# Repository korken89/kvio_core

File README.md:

# KVision Core - Visual Inertial Core

KVision core is an FPGA based Visual Inertial Odometry accelerator.

More info to come.

---

## Contributors

List of contributors in alphabetical order:

* Emil Fresk ([@korken89](https://github.com/korken89))

---

## License

The hardware is OSHW using the Cern-OHL license.

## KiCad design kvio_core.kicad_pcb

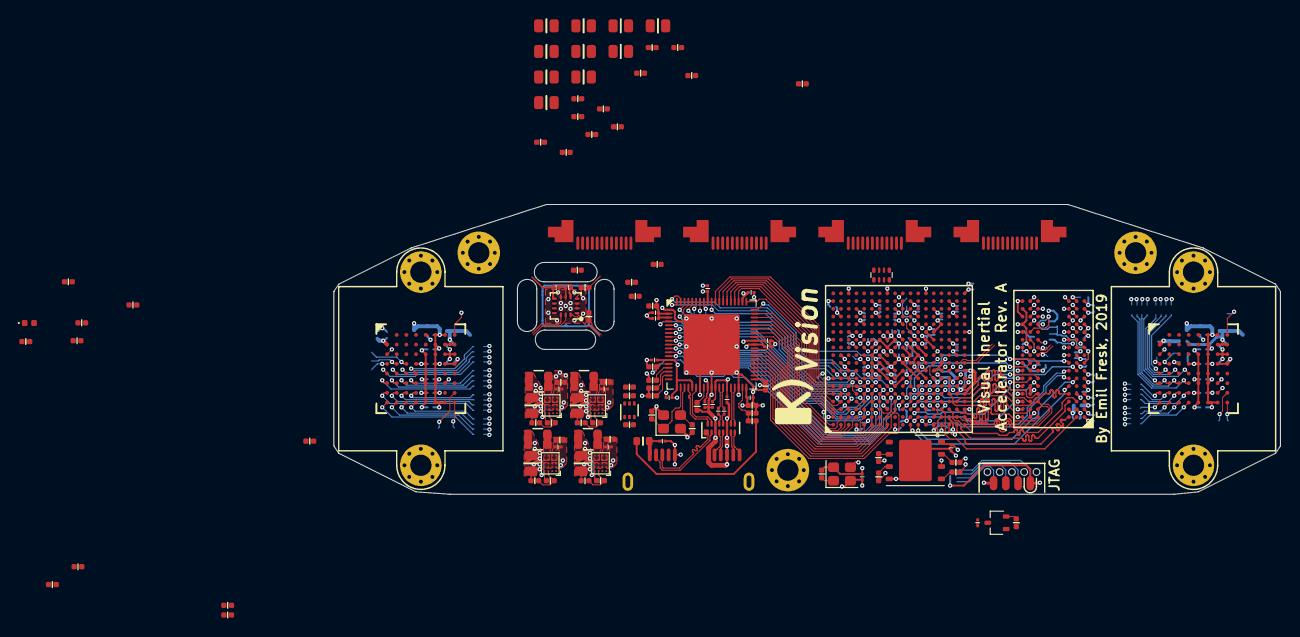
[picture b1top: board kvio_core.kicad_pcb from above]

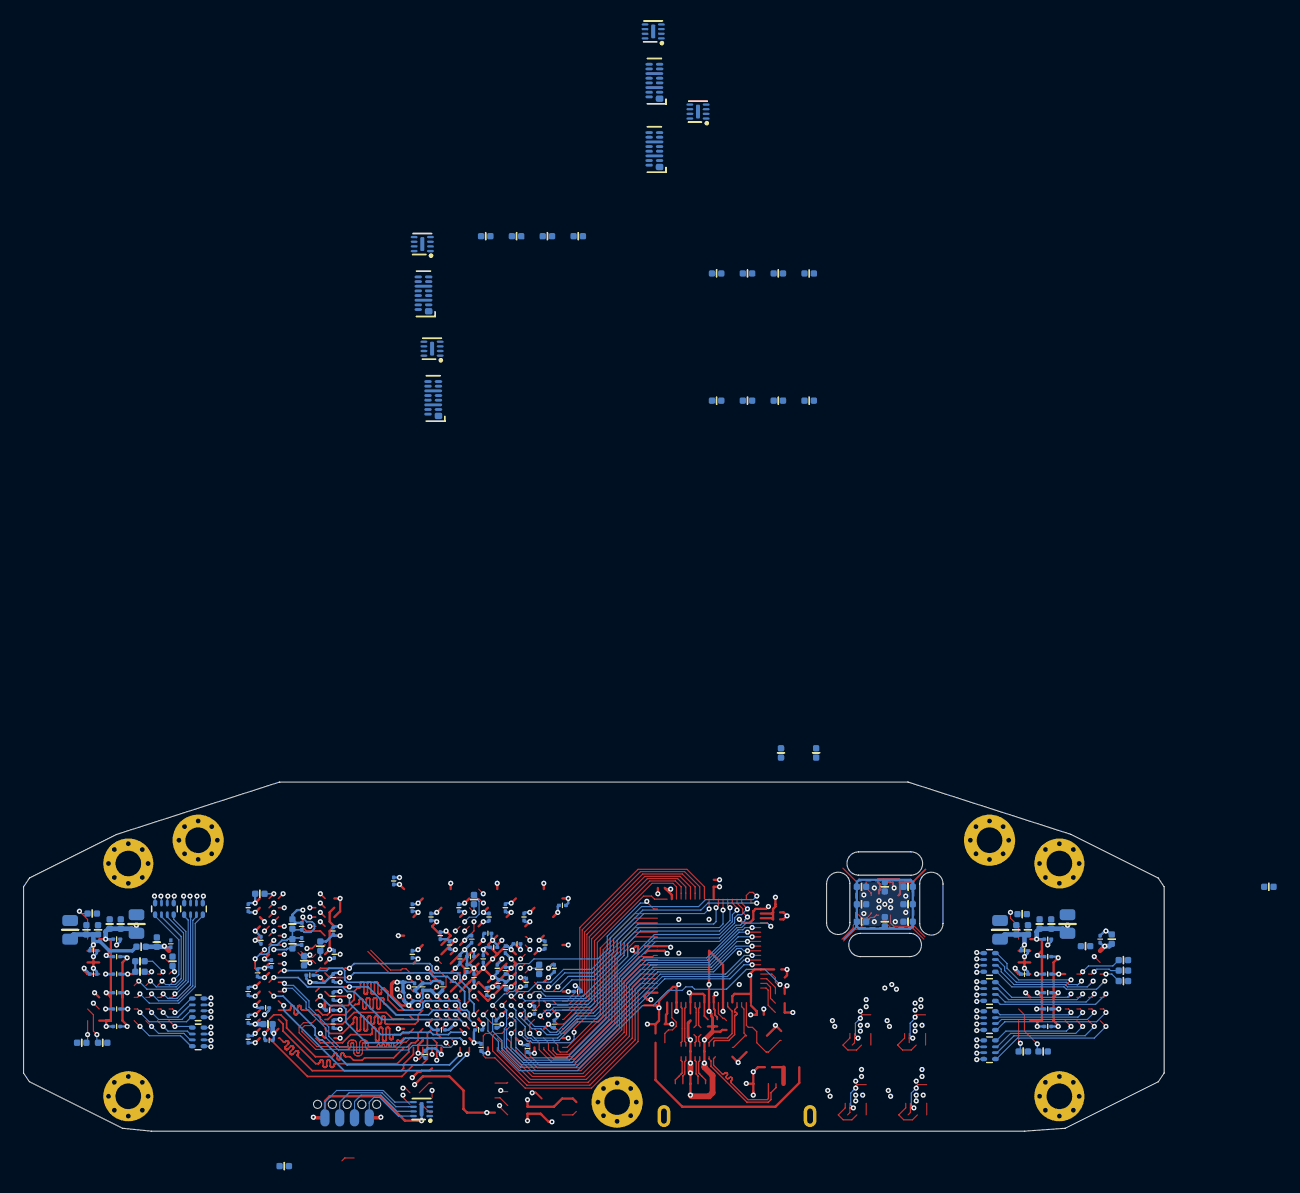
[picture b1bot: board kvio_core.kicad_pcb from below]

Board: 6 copper layers, 98.0 x 30.0 mm, 287 parts (154 on the bottom side), 316 nets.

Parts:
C101, C215, C216, C220, C221, C223, C224, C226, C227, C229, C230, C231, C232, C233, C234, C235, C236, C237, C240, C241, C243, C244, C245, C248, C249, C251, C252, C253, C254, C255, C261, C262, C263, C264, C265, C266, C267, C268, C269, C270, C272, C275, C278, C281, C284, C285, C301, C302, C1105, C1106, C1110, C1111, C1112, C1113, C1114, C1115, C1116, C1201, C1202, C1204, C1206, C1207, C1208, C1209, C1210, C1211, C1212, C1213, C1214, C1215, C1216, C1217, C1218, C1219, C1220, C1221, C1222, C1301, C1302, C1303, C1306, C1308, C1309, C1310, C1313, C1314, C1315, C1316, C1317, C1318, C1320, C1321, C1405, C1406, C1410, C1411, C1412, C1413, C1414, C1415, C1416: 0.1u; C_0201
C201, C202, C203, C204, C207, C208, C209, C214, C238, C239, C273, C276, C279, C282, C1101, C1104, C1401, C1404: 47u; C_0805
C205, C206, C210, C211, C212, C213, C217, C218, C219, C225, C228, C246, C247, C401, C801, C901, C1001, C1102, C1103, C1107, C1108, C1109, C1203, C1205, C1305, C1307, C1319, C1402, C1403, C1407, C1408, C1409: 4.7u; C_0402
C271, C274, C277, C280: 10u; C_0402
C1311, C1312: 18p; C_0402
D301: GREEN; LED_0402_1005Metric
FB201, FB401, FB801, FB901, FB1001, FB1101, FB1201, FB1401: Ferrite_Bead_Small; R_0402
FB1301: BLM18KG102SH1D; R_0603
H101, H102, H103: MountingHole_Pad; MountingHole_2.2mm_M2_Pad_Via
J401, J801, J901, J1001: 12-pin_FFC_(SFV12R); SFV12R
J1301: USB3_B_Micro; AMPHENOL-GSB343K33HR
L201, L202, L203, L204: 0.47uH; L_2025Metric
LH1101, LH1401: lens_holder; m12_20mm
Q1201: NTZD3155C; SOT-563
R101, R1101, R1102, R1103, R1104, R1302, R1303, R1306, R1401, R1402, R1403, R1404: 10k; R_0402
R201, R202, R203, R204, R205, R206, R207, R208: 0; R_0402
R301, R304, R311, R312, R313, R314, R401, R403, R801, R802, R901, R902, R1001, R1002, R1204, R1206, R1213, R1214, R1215, R1216, R1217: 100; R_0402
R302, R303, R1304, R1305: 470; R_0402
R307, R315, R316, R1205, R1207, R1208, R1210, R1307: 4.7k; R_0402
R308, R310, R1201, R1202: 1k; R_0402
R701, R702, R1105, R1106, R1301: 1.6k; R_0402
R1203: 240; R_0402
R1209, R1211, R1212, R1218, R1219, R1220, R1221, R1222: 180; R_0402
RN101, RN1101, RN1102, RN1103, RN1104, RN1401, RN1402, RN1403, RN1404: 22; R_Array_Convex_4x0402
U101: xc7a100t-csg324; CSG324_Artix7_100T
U102: 100 MHz; Crystal_SMD_2520-4Pin_2.5x2.0mm
U201, U202, U203, U204: FAN53541; WLCSP-20_1.96x1.56mm_Layout4x5_P0.4mm
U301: MX25L6433F; WSON-8-1EP_6x5mm_P1.27mm_EP3.4x4.3mm
U302: MAX809; SOT-323
U303, U402, U801, U901, U1001: IP4254CZ8-4-TTL; UDFN-8-1EP_1.7x1.35mm_P0.4mm_EP0.4x1.2mm
U304: SOICbite_JTAG; SOICbiteSmall
U401, U802, U902, U1002, U1302: EMI8143; XDFN-16_1.35x3.5mm
U1101, U1401: AR0135CS
U1201: MT41J128M16JT-125:K; BGA-96_8.0x14.0mm_DDR16
U1202: ASM330LHH; LGA-14-2.5x3
U1301: FT601Q; QFN-76-1EP_9x9mm_P0.4mm_EP5.8x6.3mm
Y1301: Crystal_GND24_Small; Crystal_SMD_2520-4Pin_2.5x2.0mm

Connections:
+1V0: C209.1, C214.1, C219.1, C225.1, C231.1, C237.1, C239.1, C245.1, C253.1, C255.1, C261.1, C263.1, C266.1, C267.1, C268.1, C269.1, C270.1, C282.1, L204.2, R207.1, U101.F8, U101.F10, U101.G7, U101.G9, U101.G11, U101.H8, U101.J7, U101.J11, U101.K8, U101.L7, U101.L11, U101.M8, U101.M10, U101.N7, U101.N9, U101.N11, U204.A4
+1V5: C201.1, C205.1, C210.1, C215.1, C220.1, C226.1, C232.1, C240.1, C248.1, C279.1, L203.2, R205.1, U101.K4, U101.N3, U101.P6, U101.T2, U101.U5, U101.V8, U203.A4
+1V8: C203.1, C207.1, C212.1, C217.1, C223.1, C229.1, C235.1, C238.1, C243.1, C246.1, C247.1, C251.1, C254.1, C262.1, C264.1, C265.1, C276.1, C1101.1, C1102.1, C1103.1, C1105.1, C1106.1, C1110.1, C1111.1, C1115.1, C1116.1, C1401.1, C1402.1, C1403.1, C1405.1, C1406.1, C1410.1, C1411.1, C1415.1, C1416.1, FB201.2, L202.2, R203.1, R701.2, R702.2, R1105.2, R1106.2, U101.A17, U101.C13, U101.D16, U101.E8, U101.F12, U101.G15, U101.H12, U101.H18, U101.K12, U101.K14, U101.M12, U202.A4, U1101.A6, U1101.A7, U1101.B6, U1101.C6, U1101.D6, U1101.E6, U1101.F6, U1101.G6, U1101.H6, U1101.H7, U1401.A6, U1401.A7, U1401.B6, U1401.C6, U1401.D6, U1401.E6, U1401.F6, U1401.G6, U1401.H6, U1401.H7
+3V3: C101.1, C202.1, C204.1, C206.1, C208.1, C211.1, C213.1, C216.1, C218.1, C221.1, C224.1, C227.1, C228.1, C230.1, C233.1, C234.1, C236.1, C241.1, C244.1, C249.1, C252.1, C273.1, C284.1, C301.2, C302.2, C1305.1, C1306.1, C1308.1, C1309.1, C1313.1, C1314.1, C1316.1, C1317.1, FB1201.2, L201.2, R101.1, R201.1, R302.2, R307.1, R308.1, R315.1, R316.1, R1302.1, U101.A7, U101.B10, U101.C3, U101.D6, U101.F2, U101.G5, U101.J1, U101.L17, U101.N13, U101.P8, U101.P12, U101.P16, U101.R9, U101.T12, U101.U15, U101.V18, U102.4, U201.A4, U301.8, U302.3, U1301.14, U1301.20, U1301.24, U1301.28, U1301.38, U1301.49, U1301.59, U1301.68
/CAM0_CLK: RN101.8, U1401.C1
/CAM0_CLK_P: RN101.1, U101.F18
/CAM0_D0: RN1402.8, U101.B14
/CAM0_D1: RN1402.7, U101.B12
/CAM0_D2: RN1402.6, U101.B11
/CAM0_D3: RN1402.5, U101.A11
/CAM0_D4: RN1403.8, U101.F13
/CAM0_D5: RN1403.7, U101.F14
/CAM0_D6: RN1403.6, U101.D12
/CAM0_D7: RN1403.5, U101.D13
/CAM0_D8: RN1404.8, U101.B16
/CAM0_D9: RN1404.7, U101.B17
/CAM0_D10: RN1404.6, U101.A15
/CAM0_D11: RN1404.5, U101.A16
/CAM0_FLASH: RN1401.1, U101.A18
/CAM0_FV: RN1401.3, U101.A13
/CAM0_LV: RN1401.4, U101.A14
/CAM0_PIXCLK: RN1401.2, U101.D15
/CAM0_RESET: R1404.1, U101.C12, U1401.H8
/CAM0_SCLK: R702.1, U101.E16, U1401.D2
/CAM0_SDATA: R701.1, U101.E15, U1401.D3
/CAM0_TRIGGER: RN101.7, U1401.G7
/CAM0_TRIGGER_P: RN101.2, U101.B18
/CAM1_CLK: RN101.6, U1101.C1
/CAM1_CLK_P: RN101.3, U101.G18
/CAM1_D0: RN1102.8, U101.H16
/CAM1_D1: RN1102.7, U101.G16
/CAM1_D2: RN1102.6, U101.F15
/CAM1_D3: RN1102.5, U101.F16
/CAM1_D4: RN1103.8, U101.H14
/CAM1_D5: RN1103.7, U101.G14
/CAM1_D6: RN1103.6, U101.E17
/CAM1_D7: RN1103.5, U101.D17
/CAM1_D8: RN1104.8, U101.K13
/CAM1_D9: RN1104.7, U101.J13
/CAM1_D10: RN1104.6, U101.H17
/CAM1_D11: RN1104.5, U101.G17
/CAM1_FLASH: RN1101.1, U101.C17
/CAM1_FV: RN1101.3, U101.J14
/CAM1_LV: RN1101.4, U101.H15
/CAM1_PIXCLK: RN1101.2, U101.C15
/CAM1_RESET: R1101.1, U101.B13, U1101.H8
/CAM1_SCLK: R1106.1, U101.D18, U1101.D2
/CAM1_SDATA: R1105.1, U101.E18, U1101.D3
/CAM1_TRIGGER: RN101.5, U1101.G7
/CAM1_TRIGGER_P: RN101.4, U101.C16
/Camera 1/5V_CAM: C401.1, FB401.1, J401.12
/Camera 1/CLK_N: R403.2, U401.12
/Camera 1/CLK_P: R403.1, U401.13
/Camera 1/CLK_P_N: J401.5, U401.5
/Camera 1/CLK_P_P: J401.6, U401.4
/Camera 1/D1_N: R401.2, U401.9
/Camera 1/D1_P: R401.1, U401.10
/Camera 1/D1_P_N: J401.2, U401.8
/Camera 1/D1_P_P: J401.3, U401.7
/Camera 1/IO1_P: J401.8, U402.8
/Camera 1/IO2_P: J401.9, U402.7
/Camera 1/SCL_P: J401.11, U402.5
/Camera 1/SDA_P: J401.10, U402.6
/Camera 2/5V_CAM: C801.1, FB801.1, J801.12
/Camera 2/CLK_N: R802.2, U802.12
/Camera 2/CLK_P: R802.1, U802.13
/Camera 2/CLK_P_N: J801.5, U802.5
/Camera 2/CLK_P_P: J801.6, U802.4
/Camera 2/D1_N: R801.2, U802.9
/Camera 2/D1_P: R801.1, U802.10
/Camera 2/D1_P_N: J801.2, U802.8
/Camera 2/D1_P_P: J801.3, U802.7
/Camera 2/IO1_P: J801.8, U801.8
/Camera 2/IO2_P: J801.9, U801.7
/Camera 2/SCL_P: J801.11, U801.5
/Camera 2/SDA_P: J801.10, U801.6
/Camera 3/5V_CAM: C901.1, FB901.1, J901.12
/Camera 3/CLK_N: R902.2, U902.12
/Camera 3/CLK_P: R902.1, U902.13
/Camera 3/CLK_P_N: J901.5, U902.5
/Camera 3/CLK_P_P: J901.6, U902.4
/Camera 3/D1_N: R901.2, U902.9
/Camera 3/D1_P: R901.1, U902.10
/Camera 3/D1_P_N: J901.2, U902.8
/Camera 3/D1_P_P: J901.3, U902.7
/Camera 3/IO1_P: J901.8, U901.8
/Camera 3/IO2_P: J901.9, U901.7
/Camera 3/SCL_P: J901.11, U901.5
/Camera 3/SDA_P: J901.10, U901.6
/Camera 4/5V_CAM: C1001.1, FB1001.1, J1001.12
/Camera 4/CLK_N: R1002.2, U1002.12
/Camera 4/CLK_P: R1002.1, U1002.13
/Camera 4/CLK_P_N: J1001.5, U1002.5
/Camera 4/CLK_P_P: J1001.6, U1002.4
/Camera 4/D1_N: R1001.2, U1002.9
/Camera 4/D1_P: R1001.1, U1002.10
/Camera 4/D1_P_N: J1001.2, U1002.8
/Camera 4/D1_P_P: J1001.3, U1002.7
/Camera 4/IO1_P: J1001.8, U1001.8
/Camera 4/IO2_P: J1001.9, U1001.7
/Camera 4/SCL_P: J1001.11, U1001.5
/Camera 4/SDA_P: J1001.10, U1001.6
/Config/CFG_CLK: R301.1, R304.1, U301.6
/Config/CFG_CS: R307.2, U101.L13, U301.1
/Config/CFG_D0: R311.1, U101.K17
/Config/CFG_D1: R312.1, U101.K18
/Config/CFG_D2: R313.1, R316.2, U101.L14
/Config/CFG_D3: R314.1, R315.2, U101.M14
/Config/CFG_DONE: R302.1, R303.2, U101.P10
/Config/CFG_INIT_B: R310.1, U101.P7, U101.P9
/Config/CFG_PUDC: R308.2, U101.L15
/Config/SYSTEM_RESET: R310.2, U302.2
/Config/TCK: U101.E10, U303.3
/Config/TCK_P: U303.6, U304.7
/Config/TDI: U101.E11, U303.4
/Config/TDI_P: U303.5, U304.8
/Config/TDO: U101.E13, U303.2
/Config/TDO_P: U303.7, U304.6
/Config/TMS: U101.E12, U303.1
/Config/TMS_P: U303.8, U304.5
/DDR Memory/A0: U101.U6, U1201.N3
/DDR Memory/A1: U101.R6, U1201.P7
/DDR Memory/A2: U101.V7, U1201.P3
/DDR Memory/A3: U101.V6, U1201.N2
/DDR Memory/A4: U101.T8, U1201.P8
/DDR Memory/A5: U101.P5, U1201.P2
/DDR Memory/A6: U101.R8, U1201.R8
/DDR Memory/A7: U101.N5, U1201.R2
/DDR Memory/A8: U101.R7, U1201.T8
/DDR Memory/A9: U101.N6, U1201.R3
/DDR Memory/A10: U101.P4, U1201.L7
/DDR Memory/A11: U101.N4, U1201.R7
/DDR Memory/A12: U101.U7, U1201.N7
/DDR Memory/A13: U101.M6, U1201.T3
/DDR Memory/BA0: U101.R5, U1201.M2
/DDR Memory/BA1: U101.U8, U1201.N8
/DDR Memory/BA2: U101.P3, U1201.M3
/DDR Memory/CAS_N: U101.R2, U1201.K3
/DDR Memory/CK_E: U101.T6, U1201.K9
/DDR Memory/CK_N: R1204.2, U101.V9, U1201.K7
/DDR Memory/CK_P: R1204.1, U101.U9, U1201.J7
/DDR Memory/CS_N: U101.P2, U1201.L2
/DDR Memory/DDR3_VDD: C1201.1, C1203.1, C1204.1, C1206.1, C1207.2, C1208.1, C1210.1, C1211.2, C1212.1, C1213.2, C1214.1, C1215.2, C1216.1, C1217.2, C1218.1, C1219.2, C1220.1, C1221.2, R1201.1, U1201.A1, U1201.A8, U1201.B2, U1201.C1, U1201.C9, U1201.D2, U1201.D9, U1201.E9, U1201.F1, U1201.G7, U1201.H2, U1201.H9, U1201.K2, U1201.K8, U1201.N1, U1201.N9, U1201.R1, U1201.R9
/DDR Memory/DQ0: U101.L1, U1201.E3
/DDR Memory/DQ1: U101.L4, U1201.F7
/DDR Memory/DQ2: U101.M1, U1201.F2
/DDR Memory/DQ3: U101.M3, U1201.F8
/DDR Memory/DQ4: U101.K3, U1201.H3
/DDR Memory/DQ5: U101.L6, U1201.H8
/DDR Memory/DQ6: U101.L3, U1201.G2
/DDR Memory/DQ7: U101.K5, U1201.H7
/DDR Memory/DQ8: U101.V5, U1201.D7
/DDR Memory/DQ9: U101.T3, U1201.C3
/DDR Memory/DQ10: U101.U4, U1201.C8
/DDR Memory/DQ11: U101.V1, U1201.C2
/DDR Memory/DQ12: U101.U3, U1201.A7
/DDR Memory/DQ13: U101.R3, U1201.A2
/DDR Memory/DQ14: U101.T5, U1201.B8
/DDR Memory/DQ15: U101.U1, U1201.A3
/DDR Memory/LDM: U101.M2, U1201.E7
/DDR Memory/LDQS_N: U101.N1, U1201.G3
/DDR Memory/LDQS_P: U101.N2, U1201.F3
/DDR Memory/ODT: U101.R1, U1201.K1
/DDR Memory/RAS_N: U101.T1, U1201.J3
/DDR Memory/RESET_N: R1205.1, U101.K6, U1201.T2
/DDR Memory/UDM: U101.V4, U1201.D3
/DDR Memory/UDQS_N: U101.V2, U1201.B7
/DDR Memory/UDQS_P: U101.U2, U1201.C7
/DDR Memory/VREF: C1201.2, C1202.1, R1201.2, R1202.1, U1201.H1, U1201.M8
/DDR Memory/WE_N: U101.M4, U1201.L3
/DDR Memory/ZQ: R1203.1, U1201.L8
/IMU_CS: R1215.1, U101.B9
/IMU_HEATER: R1206.2, U101.C11
/IMU_INT: R1210.1, R1217.1, U101.A8
/IMU_SCK: R1214.1, U101.C9
/IMU_SDI: R1213.1, U101.D9
/IMU_SDO: R1216.1, U101.B8
/Parallel camera/D0_P: RN1402.1, U1401.H1
/Parallel camera/D1_P: RN1402.2, U1401.H2
/Parallel camera/D2_P: RN1402.3, U1401.H3
/Parallel camera/D3_P: RN1402.4, U1401.H4
/Parallel camera/D4_P: RN1403.1, U1401.G1
/Parallel camera/D5_P: RN1403.2, U1401.G2
/Parallel camera/D6_P: RN1403.3, U1401.G3
/Parallel camera/D7_P: RN1403.4, U1401.G4
/Parallel camera/D8_P: RN1404.1, U1401.F1
/Parallel camera/D9_P: RN1404.2, U1401.F2
/Parallel camera/D10_P: RN1404.3, U1401.F3
/Parallel camera/D11_P: RN1404.4, U1401.F4
/Parallel camera/FLASH_P: RN1401.8, U1401.E4
/Parallel camera/FV_P: RN1401.6, U1401.E2
/Parallel camera/LV_P: RN1401.5, U1401.E1
/Parallel camera/PIXCLK_P: RN1401.7, U1401.E3
/Parallel camera/SADDR: R1402.1, U1401.D1
/Parallel camera/STANDBY: R1401.1, U1401.A8
/Parallel camera/VPLL: C1407.1, C1412.1, FB1401.1, U1401.B1
/Parallel camera/~OE: R1403.1, U1401.G8
/Power/SW10: L204.1, U204.D3, U204.D4, U204.E3, U204.E4
/Power/SW13: L203.1, U203.D3, U203.D4, U203.E3, U203.E4
/Power/SW18: L202.1, U202.D3, U202.D4, U202.E3, U202.E4
/Power/SW33: L201.1, U201.D3, U201.D4, U201.E3, U201.E4
/Power/VCCADC: C285.1, FB201.1, U101.H10
/Power/VIN: C271.1, C272.1, C274.1, C275.1, C277.1, C278.1, C280.1, C281.1, U201.D1, U201.D2, U201.E1, U201.E2, U202.D1, U202.D2, U202.E1, U202.E2, U203.D1, U203.D2, U203.E1, U203.E2, U204.D1, U204.D2, U204.E1, U204.E2
/Sensors/HEATER_SIG: Q1201.5, R1206.1, R1207.1
/Sensors/IMU_CS_P: R1215.2, U1202.12
/Sensors/IMU_HEATER: Q1201.6, R1209.1, R1211.1, R1212.1, R1218.1, R1219.1, R1220.1, R1221.1, R1222.1
/Sensors/IMU_INT_P: R1217.2, U1202.4
/Sensors/IMU_PWR: C1205.1, C1209.1, C1222.1, FB1201.1, U1202.5, U1202.8
/Sensors/IMU_SCK_P: R1214.2, U1202.13
/Sensors/IMU_SDI_P: R1213.2, U1202.14
/Sensors/IMU_SDO_P: R1216.2, U1202.1
/Sensors/V_HEATER: Q1201.1, R1208.1
/USB3 Interface/BE_0: U101.C5, U1301.4
/USB3 Interface/BE_1: U101.E6, U1301.5
/USB3 Interface/BE_2: U101.E5, U1301.6
/USB3 Interface/BE_3: U101.D4, U1301.7
/USB3 Interface/CLK: U101.E3, U1301.58
/USB3 Interface/D2_N: J1301.2, U1302.2
/USB3 Interface/D2_P: J1301.3, U1302.1
/USB3 Interface/DATA_0: U101.J4, U1301.40
/USB3 Interface/DATA_1: U101.G3, U1301.41
/USB3 Interface/DATA_2: U101.H1, U1301.42
/USB3 Interface/DATA_3: U101.H2, U1301.43
/USB3 Interface/DATA_4: U101.G1, U1301.44
/USB3 Interface/DATA_5: U101.G2, U1301.45
/USB3 Interface/DATA_6: U101.F1, U1301.46
/USB3 Interface/DATA_7: U101.E1, U1301.47
/USB3 Interface/DATA_8: U101.E2, U1301.50
/USB3 Interface/DATA_9: U101.D2, U1301.51
/USB3 Interface/DATA_10: U101.C1, U1301.52
/USB3 Interface/DATA_11: U101.C2, U1301.53
/USB3 Interface/DATA_12: U101.B1, U1301.54
/USB3 Interface/DATA_13: U101.B2, U1301.55
/USB3 Interface/DATA_14: U101.A1, U1301.56
/USB3 Interface/DATA_15: U101.H5, U1301.57
/USB3 Interface/DATA_16: U101.B3, U1301.60
/USB3 Interface/DATA_17: U101.A3, U1301.61
/USB3 Interface/DATA_18: U101.B4, U1301.62
/USB3 Interface/DATA_19: U101.A4, U1301.63
/USB3 Interface/DATA_20: U101.A5, U1301.64
/USB3 Interface/DATA_21: U101.B6, U1301.65
/USB3 Interface/DATA_22: U101.A6, U1301.66
/USB3 Interface/DATA_23: U101.B7, U1301.67
/USB3 Interface/DATA_24: U101.D8, U1301.69
/USB3 Interface/DATA_25: U101.D7, U1301.70
/USB3 Interface/DATA_26: U101.D5, U1301.71
/USB3 Interface/DATA_27: U101.E7, U1301.72
/USB3 Interface/DATA_28: U101.C4, U1301.73
/USB3 Interface/DATA_29: U101.C6, U1301.74
/USB3 Interface/DATA_30: U101.F6, U1301.75
/USB3 Interface/DATA_31: U101.C7, U1301.76
/USB3 Interface/D_N: U1301.25, U1302.15
/USB3 Interface/D_P: U1301.23, U1302.16
/USB3 Interface/GLCLK_100MHZ: U101.D3, U102.3
/USB3 Interface/OE_N: U101.H4, U1301.13
/USB3 Interface/RD_N: U101.G6, U1301.12
/USB3 Interface/RESET: R1303.2, U101.J5, U1301.15
/USB3 Interface/RREF: R1301.1, U1301.27
/USB3 Interface/RX2_N: J1301.9, U1302.7
/USB3 Interface/RX2_P: J1301.10, U1302.8
/USB3 Interface/RXF_N: U101.G4, U1301.9
/USB3 Interface/RX_N: U1301.34, U1302.10
/USB3 Interface/RX_P: U1301.35, U1302.9
/USB3 Interface/SIWU_N: U101.F3, U1301.10
/USB3 Interface/TX2_N: J1301.6, U1302.4
/USB3 Interface/TX2_P: J1301.7, U1302.5
/USB3 Interface/TXD_N: C1301.2, U1302.13
/USB3 Interface/TXD_P: C1302.2, U1302.12
/USB3 Interface/TXE_N: U101.F5, U1301.8
/USB3 Interface/TX_N: C1301.1, U1301.31
/USB3 Interface/TX_P: C1302.1, U1301.32
/USB3 Interface/VBUS: FB1301.2, R1307.1
/USB3 Interface/VBUS_SENSE: R1306.1, R1307.2, U1301.37
/USB3 Interface/VUSB_IN: C1303.2, FB1301.1, J1301.1
/USB3 Interface/WAKEUP: R1302.2, U1301.16
/USB3 Interface/WR_N: U101.F4, U1301.11
/USB3 Interface/XI: C1311.1, U1301.21, Y1301.1
/USB3 Interface/XO: C1312.1, U1301.22, Y1301.3
/sheet5D568411/D0_P: RN1102.1, U1101.H1
/sheet5D568411/D1_P: RN1102.2, U1101.H2
/sheet5D568411/D2_P: RN1102.3, U1101.H3
/sheet5D568411/D3_P: RN1102.4, U1101.H4
/sheet5D568411/D4_P: RN1103.1, U1101.G1
/sheet5D568411/D5_P: RN1103.2, U1101.G2
/sheet5D568411/D6_P: RN1103.3, U1101.G3
/sheet5D568411/D7_P: RN1103.4, U1101.G4
/sheet5D568411/D8_P: RN1104.1, U1101.F1
/sheet5D568411/D9_P: RN1104.2, U1101.F2
/sheet5D568411/D10_P: RN1104.3, U1101.F3
/sheet5D568411/D11_P: RN1104.4, U1101.F4
/sheet5D568411/FLASH_P: RN1101.8, U1101.E4
/sheet5D568411/FV_P: RN1101.6, U1101.E2
/sheet5D568411/LV_P: RN1101.5, U1101.E1
/sheet5D568411/PIXCLK_P: RN1101.7, U1101.E3
/sheet5D568411/SADDR: R1103.1, U1101.D1
/sheet5D568411/STANDBY: R1102.1, U1101.A8
/sheet5D568411/VPLL: C1107.1, C1112.1, FB1101.1, U1101.B1
/sheet5D568411/~OE: R1104.1, U1101.G8
GND: C101.2, C201.2, C202.2, C203.2, C204.2, C205.2, C206.2, C207.2, C208.2, C209.2, C210.2, C211.2, C212.2, C213.2, C214.2, C215.2, C216.2, C217.2, C218.2, C219.2, C220.2, C221.2, C223.2, C224.2, C225.2, C226.2, C227.2, C228.2, C229.2, C230.2, C231.2, C232.2, C233.2, C234.2, C235.2, C236.2, C237.2, C238.2, C239.2, C240.2, C241.2, C243.2, C244.2, C245.2, C246.2, C247.2, C248.2, C249.2, C251.2, C252.2, C253.2, C254.2, C255.2, C261.2, C262.2, C263.2, C264.2, C265.2, C266.2, C267.2, C268.2, C269.2, C270.2, C271.2, C272.2, C273.2, C274.2, C275.2, C276.2, C277.2, C278.2, C279.2, C280.2, C281.2, C282.2, C284.2, C285.2, C301.1, C302.1, C401.2, C801.2, C901.2, C1001.2, C1101.2, C1102.2, C1103.2, C1104.2, C1105.2, C1106.2, C1107.2, C1108.2, C1109.2, C1110.2, C1111.2, C1112.2, C1113.2, C1114.2, C1115.2, C1116.2, C1202.2, C1203.2, C1204.2, C1205.2, C1206.2, C1207.1, C1208.2, C1209.2, C1210.2, C1211.1, C1212.2, C1213.1, C1214.2, C1215.1, C1216.2, C1217.1, C1218.2, C1219.1, C1220.2, C1221.1, C1222.2, C1303.1, C1305.2, C1306.2, C1307.2, C1308.2, C1309.2, C1310.2, C1311.2, C1312.2, C1313.2, C1314.2, C1315.2, C1316.2, C1317.2, C1318.2, C1319.2, C1320.2, C1321.2, C1401.2, C1402.2, C1403.2, C1404.2, C1405.2, C1406.2, C1407.2, C1408.2, C1409.2, C1410.2, C1411.2, C1412.2, C1413.2, C1414.2, C1415.2, C1416.2, D301.1, H101.1, H102.1, H103.1, J401.0, J401.1, J401.4, J401.7, J801.0, J801.1, J801.4, J801.7, J901.0, J901.1, J901.4, J901.7, J1001.0, J1001.1, J1001.4, J1001.7, J1301.5, J1301.8, J1301.11, LH1101.1, LH1101.2, LH1401.1, LH1401.2, Q1201.4, R202.1, R204.1, R206.1, R208.1, R1101.2, R1102.2, R1103.2, R1104.2, R1202.2, R1203.2, R1205.2, R1207.2, R1209.2, R1210.2, R1211.2, R1212.2, R1218.2, R1219.2, R1220.2, R1221.2, R1222.2, R1301.2, R1303.1, R1304.1, R1305.1, R1306.2, R1401.2, R1402.2, R1403.2, R1404.2, U101.A2, U101.A12, U101.B5, U101.B15, U101.C8, U101.C18, U101.D1, U101.D11, U101.E4, U101.E14, U101.F7, U101.F9, U101.F11, U101.F17, U101.G8, U101.G10, U101.G12, U101.H3, U101.H7, U101.H9, U101.H11, U101.H13, U101.J6, U101.J8, U101.J9, U101.J10, U101.J12, U101.J16, U101.K7, U101.K9, U101.K10, U101.K11, U101.L2, U101.L8, U101.L9, U101.L10, U101.L12, U101.M5, U101.M7, U101.M9, U101.M11, U101.M15, U101.N8, U101.N10, U101.N12, U101.N18, U101.P1, U101.P11, U101.P13, U101.R4, U101.R14, U101.T7, U101.T17, U101.U10, U101.V3, U101.V13, U102.2, U201.B1, U201.B2, U201.B3, U201.B4, U201.C1, U201.C2, U201.C3, U201.C4, U202.B1, U202.B2, U202.B3, U202.B4, U202.C1, U202.C2, U202.C3, U202.C4, U203.B1, U203.B2, U203.B3, U203.B4, U203.C1, U203.C2, U203.C3, U203.C4, U204.B1, U204.B2, U204.B3, U204.B4, U204.C1, U204.C2, U204.C3, U204.C4, U301.4, U301.9, U302.1, U303.9, U304.1, U401.3, U401.6, U401.15, U401.16, U402.9, U801.9, U802.3, U802.6, U802.15, U802.16, U901.9, U902.3, U902.6, U902.15, U902.16, U1001.9, U1002.3, U1002.6, U1002.15, U1002.16, U1101.C5, U1101.C7, U1101.C8, U1101.D4, U1101.D5, U1101.E5, U1101.F5, U1101.F7, U1101.G5, U1101.H5, U1201.A9, U1201.B1, U1201.B3, U1201.B9, U1201.D1, U1201.D8, U1201.E1, U1201.E2, U1201.E8, U1201.F9, U1201.G1, U1201.G8, U1201.G9, U1201.J2, U1201.J8, U1201.M1, U1201.M9, U1201.P1, U1201.P9, U1201.T1, U1201.T9, U1202.2, U1202.3, U1202.6, U1202.7, U1301.1, U1301.26, U1301.29, U1301.36, U1301.77, U1302.3, U1302.6, U1401.C5, U1401.C7, U1401.C8, U1401.D4, U1401.D5, U1401.E5, U1401.F5, U1401.F7, U1401.G5, U1401.H5, Y1301.2, Y1301.4
unnamed: C1307.1, C1310.1, C1315.1, C1318.1, C1319.1, C1320.1, C1321.1, U1301.2, U1301.3, U1301.30, U1301.33, U1301.39, U1301.48
unnamed: D301.2, R303.1
unnamed: Q1201.2, Q1201.3, R1208.2
unnamed: R101.2, U102.1
unnamed: R201.2, R202.2, U201.A3
unnamed: R203.2, R204.2, U202.A3
unnamed: R205.2, R206.2, U203.A3
unnamed: R207.2, R208.2, U204.A3
unnamed: R301.2, U101.E9
unnamed: R304.2, U101.L16
unnamed: R311.2, U301.5
unnamed: R312.2, U301.2
unnamed: R313.2, U301.3
unnamed: R314.2, U301.7
unnamed: R1304.2, U1301.17
unnamed: R1305.2, U1301.18
VAA: C1104.1, C1108.1, C1109.1, C1113.1, C1114.1, C1404.1, C1408.1, C1409.1, C1413.1, C1414.1, FB1101.2, FB1401.2, U1101.B7, U1101.B8, U1101.D7, U1101.D8, U1401.B7, U1401.B8, U1401.D7, U1401.D8

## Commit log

2019-05-06 Settings
2019-06-30 More added
2019-07-06 More stuff
2019-07-06 More
2019-07-07 DDR3 routed, length matching left
2019-07-08 Before length matching
2019-07-08 Data groups length matched
2019-07-08 Length matching done (except CK, needs final layers)
2019-07-08 Cleaning up length tuning
2019-07-09 New length matching script
2019-07-11 Fixing for adding pad lengths
2019-07-11 Updated scripts
2019-07-11 Added pad-to-die length file
2019-07-11 New length matching
2019-07-11 Now with DDR3 1.5 mm closer
2019-07-12 Moved scripts to their own folder
2019-07-12 Updates to length matching and added GND plane for DDR3
2019-07-19 More design
2019-07-25 More additions, DDR3 caps placed
2019-07-25 More docs added and given sane names
2019-07-25 More docs
2019-07-25 Fixing with DDR3, needs retuning
2019-07-30 More layout and design
2019-07-31 Added 2 cameras via parallel interface
2019-08-01 USB3 FIFO layout done, some testing with camera connectors
2019-08-02 Added IMU
2019-08-03 Added IMU + heater, fixed USB3 FIFO lines
2019-08-05 More layout
2019-08-06 More work
2019-08-07 Added signal for global clock
